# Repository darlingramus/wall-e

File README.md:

# wall-e

## disaster (wrong chip, wrong connections, wrong everything)
## will probably do this later (also expensive)

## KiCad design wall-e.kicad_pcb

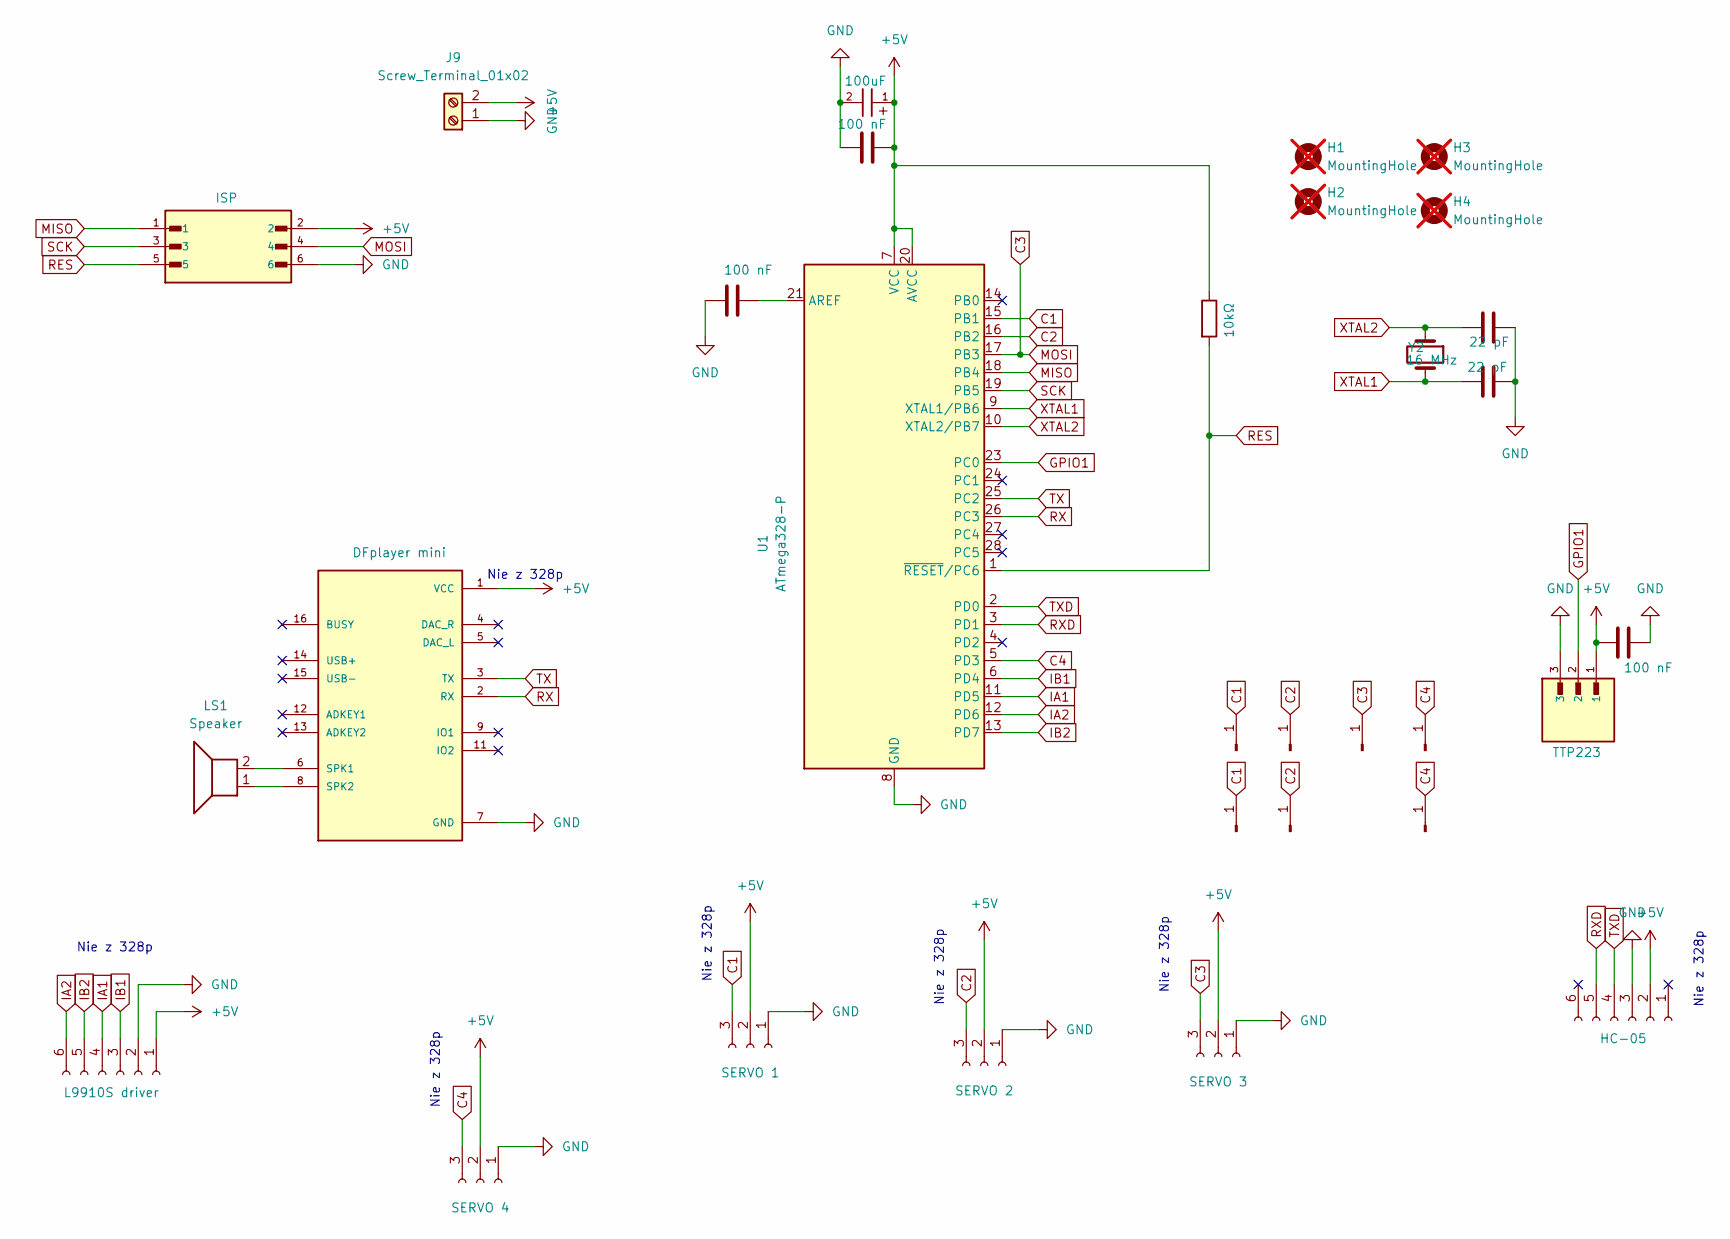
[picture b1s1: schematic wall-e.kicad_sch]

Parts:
C1, C2, C7: 100 nF; C_1206_3216Metric
C3, C4: 22 pF; C_1206_3216Metric
C6: 100uF; 100uFCap_MOD
H1, H2, H3, H4: MountingHole; MountingHole_3mm; not fitted
J1: ISP; Header2x3_MOD
J2: SERVO 1; PinHeader_1x03_P2.54mm_Vertical
J3: HC-05; PinHeader_1x06_P2.54mm_Vertical
J4: TTP223; PinHeader_1x03_P2.54mm_Vertical; PARTREV 003.001
J5: L9910S driver; PinHeader_1x06_P2.54mm_Vertical
J6: SERVO 2; PinHeader_1x03_P2.54mm_Vertical
J7: SERVO 3; PinHeader_1x03_P2.54mm_Vertical
J8: SERVO 4; PinHeader_1x03_P2.54mm_Vertical
J9: Screw_Terminal_01x02; TerminalBlock_MaiXu_MX126-5.0-02P_1x02_P5.00mm
J10, J12, J13, J14, J15, J17, J18: Conn_01x01_Pin; PinHeader_1x01_P2.54mm_Vertical
LS1: Speaker; Speaker_CUI_CMR-1206S-67
R3: 10kΩ; R_1206_3216Metric
U1: ATmega328-P; DIP-28_W7.62mm
U2: DFplayer mini; MODULE_DFR0299
Y2: 16 MHz; Crystal_HC18-U_Vertical

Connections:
+5V: C1.2, C6.1, C7.2, J1.2, J2.2, J3.2, J4.1, J5.1, J6.2, J7.2, J8.2, J9.2, R3.1, U1.7 (VCC), U1.20 (AVCC), U2.1 (VCC)
C1: J2.3, J13.1 (Pin_1_1), J14.1 (Pin_1_1), U1.15 (PB1)
C2: J6.3, J12.1 (Pin_1_1), J15.1 (Pin_1_1), U1.16 (PB2)
C3: J1.4, J7.3, J10.1 (Pin_1_1), U1.17 (PB3)
C4: J8.3, J17.1 (Pin_1_1), J18.1 (Pin_1_1), U1.5 (PD3)
GND: C1.1, C2.2, C3.1, C4.1, C6.2, C7.1, J1.6, J2.1, J3.3, J4.3, J5.2, J6.1, J7.1, J8.1, J9.1, U1.8 (GND), U1.22 (GND), U2.7 (GND), U2.10 (GND)
GPIO1: J4.2, U1.23 (PC0)
IA1: J5.4, U1.11 (PD5)
IA2: J5.6, U1.12 (PD6)
IB1: J5.3, U1.6 (PD4)
IB2: J5.5, U1.13 (PD7)
MISO: J1.1, U1.18 (PB4)
unnamed: C2.1, U1.21 (AREF)
unnamed: LS1.2, U2.6 (SPK1)
unnamed: LS1.1, U2.8 (SPK2)
RES: J1.5, R3.2, U1.1 (~RESET/PC6)
RX: U1.26 (PC3), U2.2 (RX)
RXD: J3.5, U1.3 (PD1)
SCK: J1.3, U1.19 (PB5)
TX: U1.25 (PC2), U2.3 (TX)
TXD: J3.4, U1.2 (PD0)
XTAL1: C4.2, U1.9 (XTAL1/PB6), Y2.2
XTAL2: C3.2, U1.10 (XTAL2/PB7), Y2.1

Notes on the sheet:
Nie z 328p

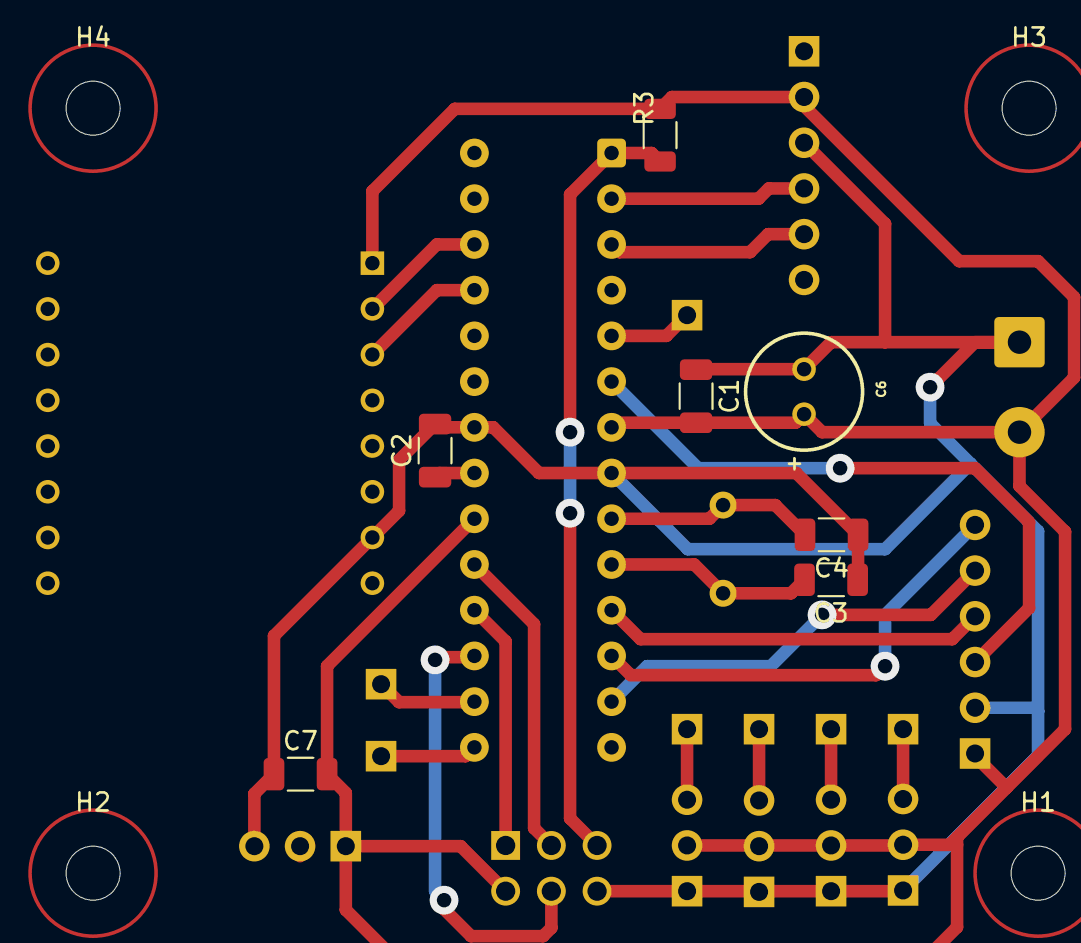
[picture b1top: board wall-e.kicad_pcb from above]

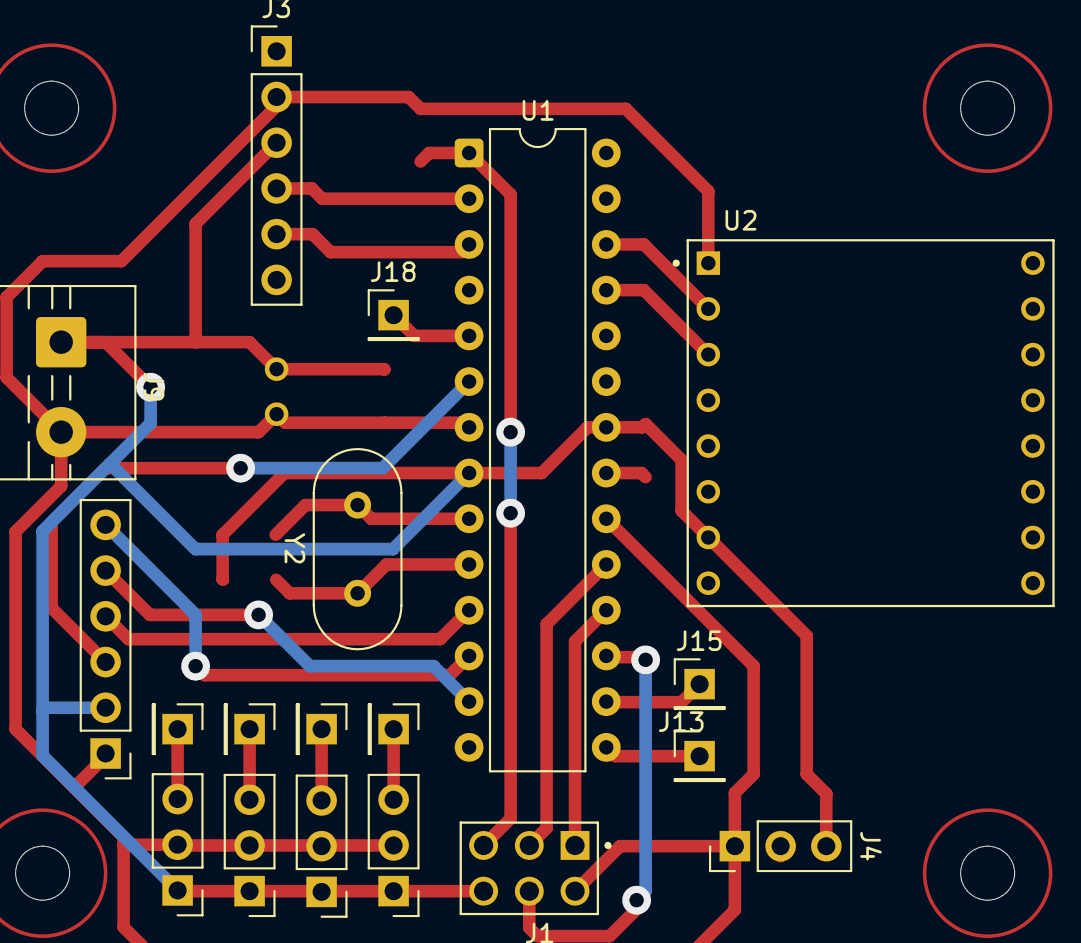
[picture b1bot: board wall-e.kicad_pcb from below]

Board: 2 copper layers, 30 parts (19 on the bottom side), 21 nets.

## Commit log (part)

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2026-06-24 wall-e schematics
